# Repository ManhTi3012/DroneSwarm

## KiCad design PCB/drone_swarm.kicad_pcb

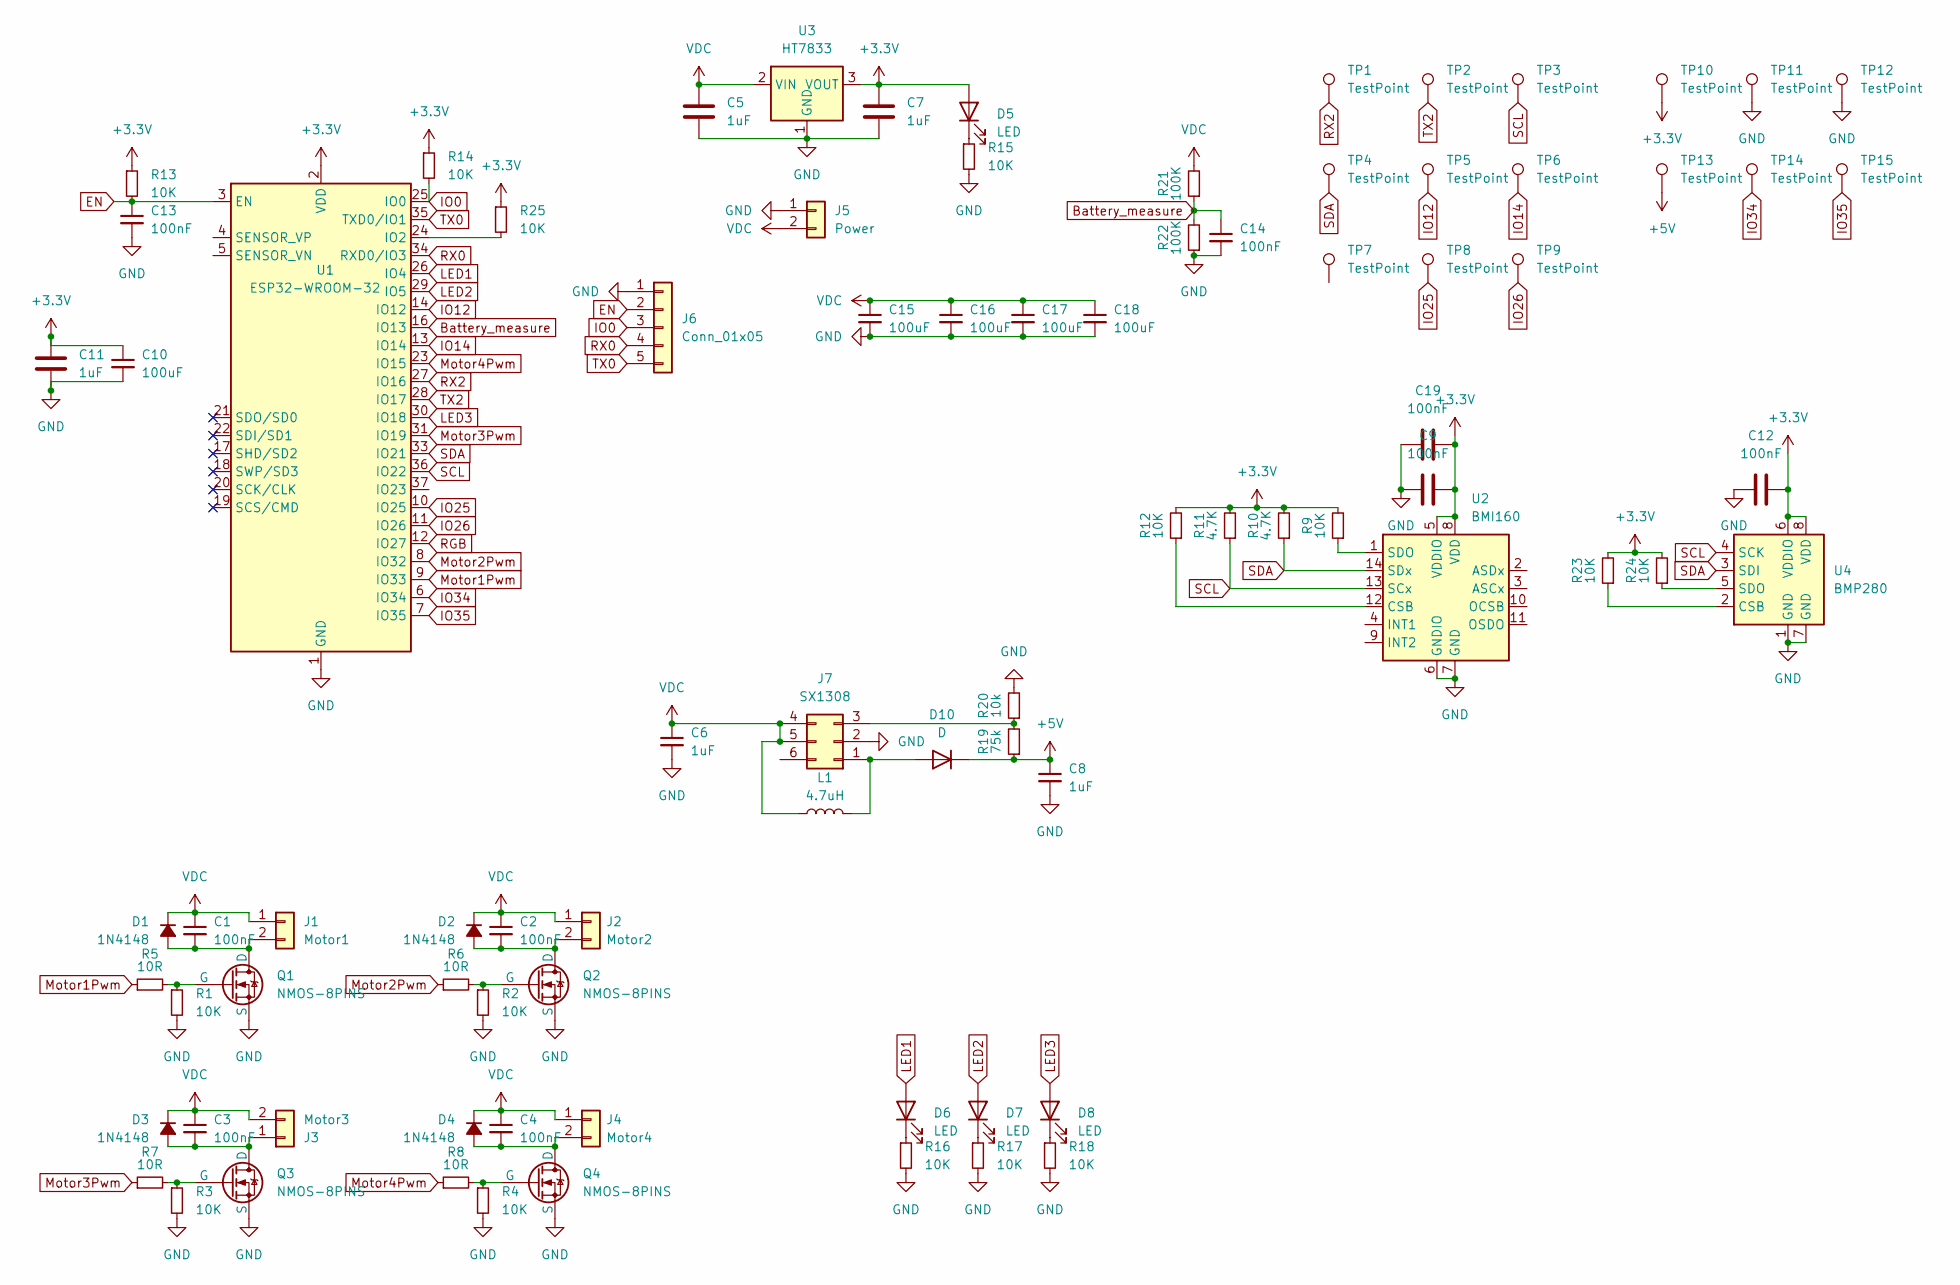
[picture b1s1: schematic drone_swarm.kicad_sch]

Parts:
C1, C2, C3, C4, C9, C12, C13, C14, C19: 100nF; C_0603_1608Metric
C5, C6, C7, C8, C11: 1uF; C_0603_1608Metric
C10, C15, C16, C17, C18: 100uF; C_1206_3216Metric
D1, D2, D3, D4: 1N4148; D_SOD-323
D5, D6, D7, D8: LED; LED_0603_1608Metric
D10: D; D_SOD-323
J1: Motor1; DualPad_1x2mm
J2: Motor2; DualPad_1x2mm
J3: Motor3; DualPad_1x2mm
J4: Motor4; DualPad_1x2mm
J5: Power; DualPad_2x3mm
J6: Conn_01x05; PinHeader_1x05_P2.00mm_Vertical
J7: SX1308; SOT-23-6
L1: 4.7uH; L_Chilisin_BMRA00040420
Q1, Q2, Q3, Q4: NMOS-8PINS; DFN8_3X3_EP_AOS
R1, R2, R3, R4, R9, R12, R13, R14, R15, R16, R17, R18, R23, R24, R25: 10K; R_0603_1608Metric
R5, R6, R7, R8: 10R; R_0603_1608Metric
R10, R11: 4.7K; R_0603_1608Metric
R19: 75k; R_0603_1608Metric
R20: 10k; R_0603_1608Metric
R21, R22: 100K; R_0603_1608Metric
TP1, TP2, TP3, TP4, TP5, TP6, TP7, TP8, TP9, TP10, TP11, TP12, TP13, TP14, TP15: TestPoint; Pad_1x1mm
U1: ESP32-WROOM-32
U2: BMI160; Bosch_LGA-14_3x2.5mm_P0.5mm
U3: HT7833; SOT-89-3
U4: BMP280; Bosch_LGA-8_2x2.5mm_P0.65mm_ClockwisePinNumbering

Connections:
+3.3V: C7.1, C9.2, C10.1, C11.1, C12.2, C19.2, D5.2 (A), R9.2, R10.2, R11.2, R12.2, R13.1, R14.1, R23.2, R24.2, R25.1, TP10.1, U1.2 (VDD), U2.5 (VDDIO), U2.8 (VDD), U3.3 (VOUT), U4.6 (VDDIO), U4.8 (VDD)
+5V: C8.1, D10.1 (K), R19.1, TP13.1
Battery_measure: C14.1, R21.1, R22.2, U1.16 (IO13)
EN: C13.1, J6.2, R13.2, U1.3 (EN)
GND: C5.2, C6.2, C7.2, C8.2, C9.1, C10.2, C11.2, C12.1, C13.2, C14.2, C15.2, C16.2, C17.2, C18.2, C19.1, J5.1, J6.1, J7.2, Q1.1 (S), Q1.2 (S), Q1.3 (S), Q2.1 (S), Q2.2 (S), Q2.3 (S), Q3.1 (S), Q3.2 (S), Q3.3 (S), Q4.1 (S), Q4.2 (S), Q4.3 (S), R1.2, R2.2, R3.2, R4.2, R15.2, R16.2, R17.2, R18.2, R20.2, R22.1, TP11.1, TP12.1, U1.1 (GND), U1.15 (GND), U1.38 (GND), U1.39 (GND), U2.6 (GNDIO), U2.7 (GND), U3.1 (GND), U4.1 (GND), U4.7 (GND)
IO0: J6.3, R14.2, U1.25 (IO0)
IO12: TP5.1, U1.14 (IO12)
IO14: TP6.1, U1.13 (IO14)
IO25: TP8.1, U1.10 (IO25)
IO26: TP9.1, U1.11 (IO26)
IO34: TP14.1, U1.6 (IO34)
IO35: TP15.1, U1.7 (IO35)
LED1: D6.2 (A), U1.26 (IO4)
LED2: D7.2 (A), U1.29 (IO5)
LED3: D8.2 (A), U1.30 (IO18)
Motor1Pwm: R5.1, U1.9 (IO33)
Motor2Pwm: R6.1, U1.8 (IO32)
Motor3Pwm: R7.1, U1.31 (IO19)
Motor4Pwm: R8.1, U1.23 (IO15)
unnamed: C1.2, D1.2 (A), J1.2, Q1.5 (D), Q1.6 (D), Q1.7 (D), Q1.8 (D)
unnamed: C2.2, D2.2 (A), J2.2, Q2.5 (D), Q2.6 (D), Q2.7 (D), Q2.8 (D)
unnamed: C3.2, D3.2 (A), J3.1, Q3.5 (D), Q3.6 (D), Q3.7 (D), Q3.8 (D)
unnamed: C4.2, D4.2 (A), J4.2, Q4.5 (D), Q4.6 (D), Q4.7 (D), Q4.8 (D)
unnamed: D5.1 (K), R15.1
unnamed: D6.1 (K), R16.1
unnamed: D7.1 (K), R17.1
unnamed: D8.1 (K), R18.1
unnamed: D10.2 (A), J7.1, L1.2
unnamed: J7.3, R19.2, R20.1
unnamed: Q1.4 (G), R1.1, R5.2
unnamed: Q2.4 (G), R2.1, R6.2
unnamed: Q3.4 (G), R3.1, R7.2
unnamed: Q4.4 (G), R4.1, R8.2
unnamed: R25.2, U1.24 (IO2)
unnamed: R12.1, U2.12 (CSB)
unnamed: R9.1, U2.1 (SDO)
unnamed: R23.1, U4.2 (CSB)
unnamed: R24.1, U4.5 (SDO)
RGB: U1.12 (IO27)
RX0: J6.4, U1.34 (RXD0/IO3)
RX2: TP1.1, U1.27 (IO16)
SCL: R11.1, TP3.1, U1.36 (IO22), U2.13 (SCx), U4.4 (SCK)
SDA: R10.1, TP4.1, U1.33 (IO21), U2.14 (SDx), U4.3 (SDI)
TX0: J6.5, U1.35 (TXD0/IO1)
TX2: TP2.1, U1.28 (IO17)
VDC: C1.1, C2.1, C3.1, C4.1, C5.1, C6.1, C15.1, C16.1, C17.1, C18.1, D1.1 (K), D2.1 (K), D3.1 (K), D4.1 (K), J1.1, J2.1, J3.2, J4.1, J5.2, J7.4, J7.5, L1.1, R21.2, U3.2 (VIN)

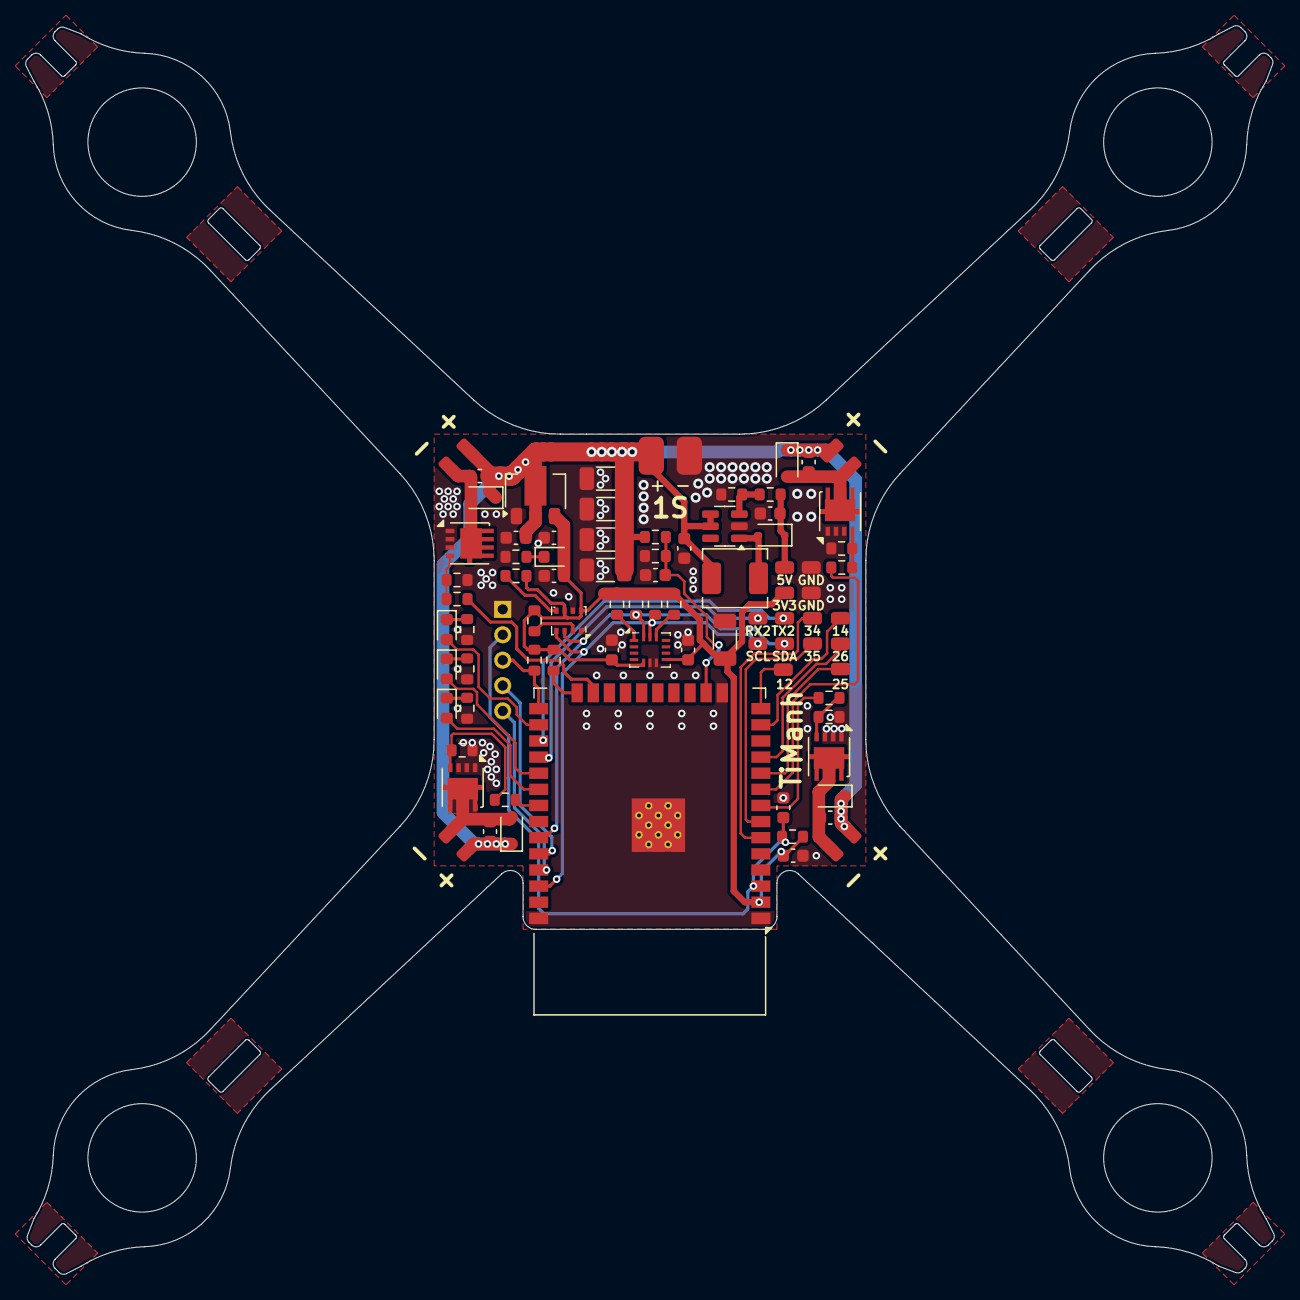
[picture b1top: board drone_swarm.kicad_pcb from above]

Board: 2 copper layers, 98.3 x 98.3 mm, 83 parts (1 on the bottom side), 45 nets.

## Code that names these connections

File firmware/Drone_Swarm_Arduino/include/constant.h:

/*
 * constant.h
 *
 *  Created on: May 30, 2025
 *      Author: Ti Manh
 */

#ifndef CONSTANT_H_
#define CONSTANT_H_

#define MAX_PWM 1023

#define LED1 4
#define LED2 5
#define LED3 18

#define MOTOR_FL 15
#define MOTOR_FR 33
#define MOTOR_BL 19
#define MOTOR_BR 32

#define PWM_FREQ 10000
#define PWM_RES 10
#endif

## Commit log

2025-07-06 Create temp
2025-09-17 update image
